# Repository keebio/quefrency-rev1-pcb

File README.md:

Quefrency Rev. 1 Keyboard PCB
=============================

Files are provided as-is, as I haven't fully had the chance to clean everything up. The working name of the Quefrency was Spectrogram, hence some of the files being marked with that name.

If anyone wants to clean things up, go ahead and submit a PR. Thanks!

License
-------
These files are released under the MIT License.

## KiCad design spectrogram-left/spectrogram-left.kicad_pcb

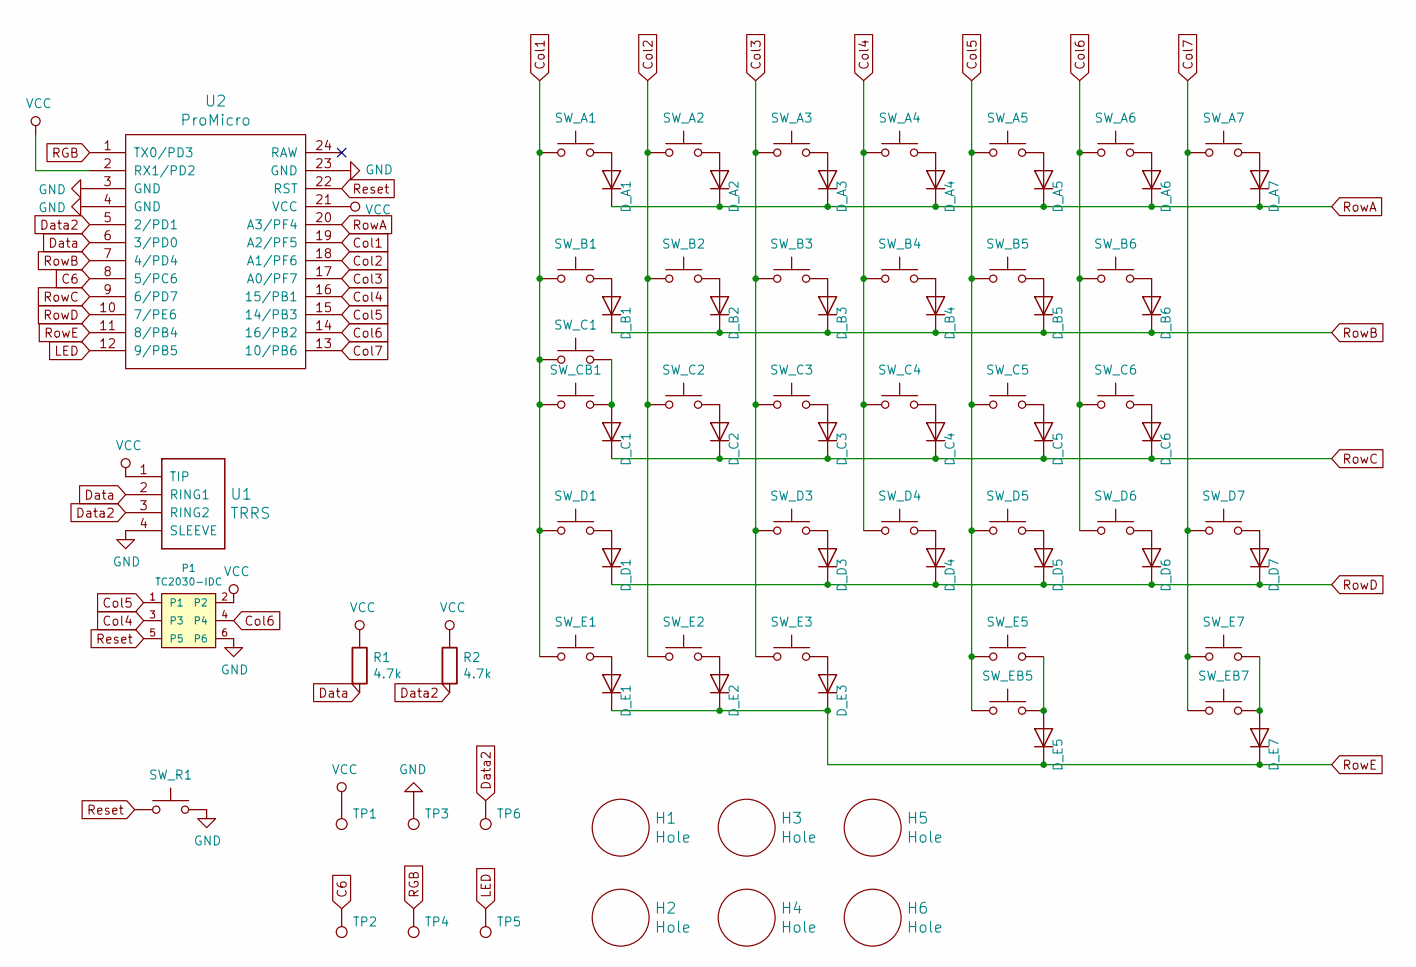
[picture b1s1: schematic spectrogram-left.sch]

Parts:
D_A1, D_A2, D_A3, D_A4, D_A5, D_A6, D_A7: D; Diode-Hybrid-Back
D_B1, D_B2, D_B3, D_B4, D_B5, D_B6: D; Diode-Hybrid-Back
D_C1, D_C2, D_C3, D_C4, D_C5, D_C6: D; Diode-Hybrid-Back
D_D1, D_D3, D_D4, D_D5, D_D6, D_D7: D; Diode-Hybrid-Back
D_E1, D_E2, D_E3, D_E5, D_E7: D; Diode-Hybrid-Back
H1, H2, H3, H4, H5, H6: Hole; MountingHole_3.2mm_M3_ISO14580_Pad
P1: TC2030-IDC; TC2030-NL_SMALL
R1, R2: 4.7k; Resistor-Hybrid-Back
SW_A1, SW_A2, SW_A3, SW_A4, SW_A5, SW_A6, SW_A7: SW_Push; MX-1U-NoLED
SW_B1: SW_Push; MX-1.5U-NoLED
SW_B2, SW_B3, SW_B4, SW_B5, SW_B6: SW_Push; MX-1U-NoLED
SW_C1: SW_Push; MX-1.75U-NoLED
SW_C2, SW_C3, SW_C4, SW_C5, SW_C6: SW_Push; MX-1U-NoLED
SW_CB1: SW_Push; MX-1.25U-NoLED
SW_D1: SW_Push; MX-2.25U-NoLED
SW_D3, SW_D4, SW_D5, SW_D6, SW_D7: SW_Push; MX-1U-NoLED
SW_E1, SW_E2, SW_E3, SW_E7: SW_Push; MX-1.25U-NoLED
SW_E5: SW_Push; MX-2.25U-ReversedStabilizers-NoLED
SW_EB5: SW_Push; MX-1.25U-NoLED
SW_EB7: SW_Push; MX-2.25U-ReversedStabilizers-NoLED
SW_R1: Reset; SW_Tactile_SPST_Angled_MJTP1117
TP1: VCC; SinglePad
TP2: C6; SinglePad
TP3: GND; SinglePad
TP4: RGB; SinglePad
TP5: LED; SinglePad
TP6: Extra Data; SinglePad
U1: TRRS; TRRS-PJ-320A
U2: ProMicro; ArduinoProMicro

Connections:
C6: TP2.1, U2.8 (5/PC6)
Col1: SW_A1.1, SW_B1.1, SW_C1.1, SW_CB1.2, SW_D1.1, SW_E1.1, U2.19 (A2/PF5)
Col2: SW_A2.1, SW_B2.1, SW_C2.1, SW_E2.1, U2.18 (A1/PF6)
Col3: SW_A3.1, SW_B3.1, SW_C3.1, SW_D3.1, SW_E3.1, U2.17 (A0/PF7)
Col4: P1.3, SW_A4.1, SW_B4.1, SW_C4.1, SW_D4.1, U2.16 (15/PB1)
Col5: P1.1, SW_A5.1, SW_B5.1, SW_C5.1, SW_D5.1, SW_E5.1, SW_EB5.1, U2.15 (14/PB3)
Col6: P1.4, SW_A6.1, SW_B6.1, SW_C6.1, SW_D6.1, U2.14 (16/PB2)
Col7: SW_A7.1, SW_D7.1, SW_E7.1, SW_EB7.1, U2.13 (10/PB6)
Data: R1.2, U1.2 (RING1), U2.6 (3/PD0)
Data2: R2.2, TP6.1, U1.3 (RING2), U2.5 (2/PD1)
GND: P1.6, SW_R1.2, TP3.1, U1.4 (SLEEVE), U2.3 (GND), U2.4 (GND), U2.23 (GND)
LED: TP5.1, U2.12 (9/PB5)
unnamed: D_A1.2 (A), SW_A1.2
unnamed: D_A2.2 (A), SW_A2.2
unnamed: D_A3.2 (A), SW_A3.2
unnamed: D_A4.2 (A), SW_A4.2
unnamed: D_A5.2 (A), SW_A5.2
unnamed: D_A6.2 (A), SW_A6.2
unnamed: D_A7.2 (A), SW_A7.2
unnamed: D_B1.2 (A), SW_B1.2
unnamed: D_B2.2 (A), SW_B2.2
unnamed: D_B3.2 (A), SW_B3.2
unnamed: D_B4.2 (A), SW_B4.2
unnamed: D_B5.2 (A), SW_B5.2
unnamed: D_B6.2 (A), SW_B6.2
unnamed: D_C1.2 (A), SW_C1.2, SW_CB1.1
unnamed: D_C2.2 (A), SW_C2.2
unnamed: D_C3.2 (A), SW_C3.2
unnamed: D_C4.2 (A), SW_C4.2
unnamed: D_C5.2 (A), SW_C5.2
unnamed: D_C6.2 (A), SW_C6.2
unnamed: D_D1.2 (A), SW_D1.2
unnamed: D_D3.2 (A), SW_D3.2
unnamed: D_D4.2 (A), SW_D4.2
unnamed: D_D5.2 (A), SW_D5.2
unnamed: D_D6.2 (A), SW_D6.2
unnamed: D_D7.2 (A), SW_D7.2
unnamed: D_E1.2 (A), SW_E1.2
unnamed: D_E2.2 (A), SW_E2.2
unnamed: D_E3.2 (A), SW_E3.2
unnamed: D_E5.2 (A), SW_E5.2, SW_EB5.2
unnamed: D_E7.2 (A), SW_E7.2, SW_EB7.2
RGB: TP4.1, U2.1 (TX0/PD3)
Reset: P1.5, SW_R1.1, U2.22 (RST)
RowA: D_A1.1 (K), D_A2.1 (K), D_A3.1 (K), D_A4.1 (K), D_A5.1 (K), D_A6.1 (K), D_A7.1 (K), U2.20 (A3/PF4)
RowB: D_B1.1 (K), D_B2.1 (K), D_B3.1 (K), D_B4.1 (K), D_B5.1 (K), D_B6.1 (K), U2.7 (4/PD4)
RowC: D_C1.1 (K), D_C2.1 (K), D_C3.1 (K), D_C4.1 (K), D_C5.1 (K), D_C6.1 (K), U2.9 (6/PD7)
RowD: D_D1.1 (K), D_D3.1 (K), D_D4.1 (K), D_D5.1 (K), D_D6.1 (K), D_D7.1 (K), U2.10 (7/PE6)
RowE: D_E1.1 (K), D_E2.1 (K), D_E3.1 (K), D_E5.1 (K), D_E7.1 (K), U2.11 (8/PB4)
VCC: P1.2, R1.1, R2.1, TP1.1, U1.1 (TIP), U2.2 (RX1/PD2), U2.21 (VCC)

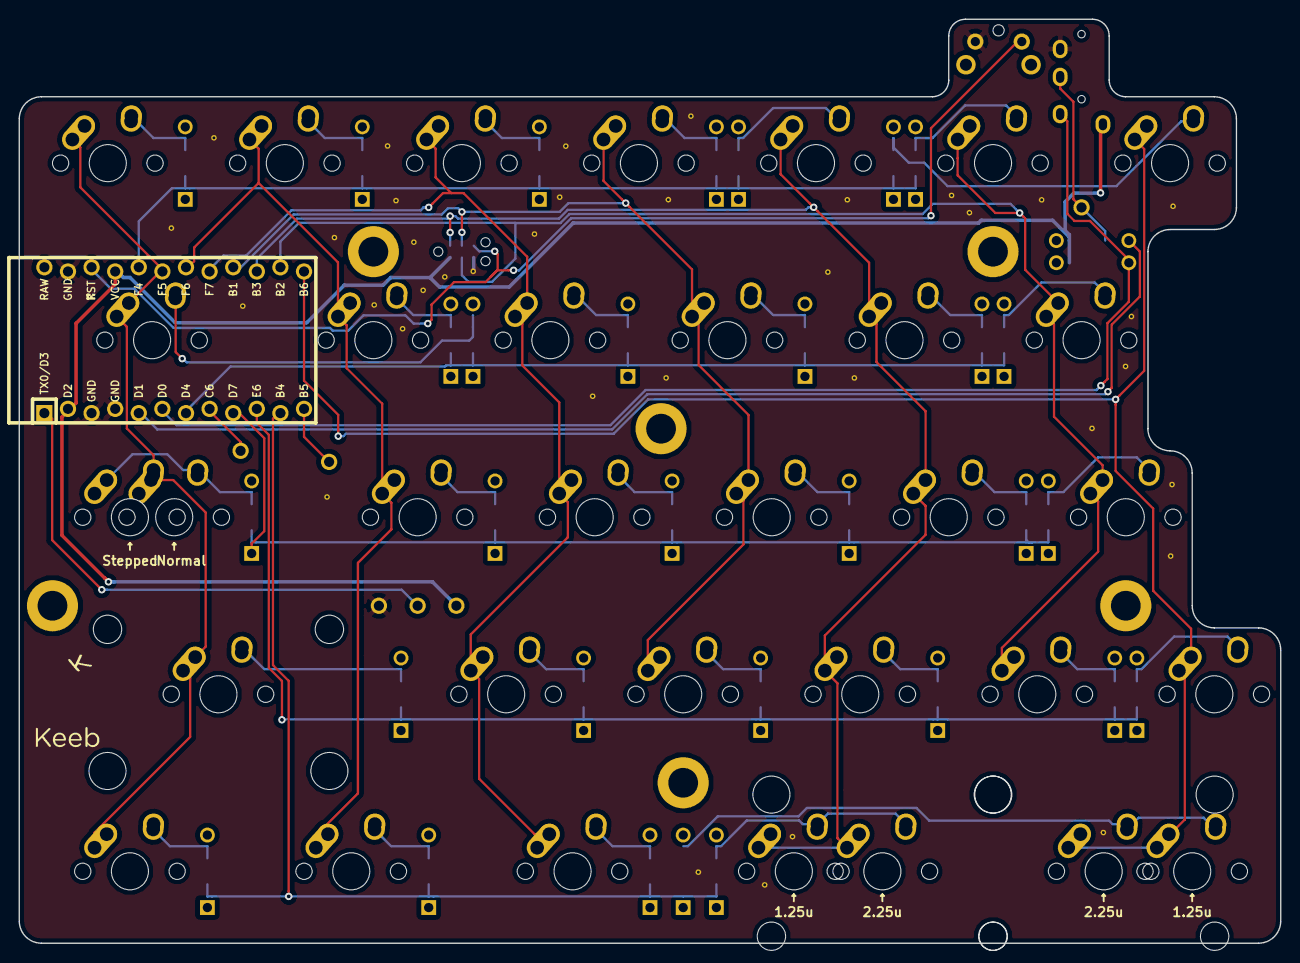
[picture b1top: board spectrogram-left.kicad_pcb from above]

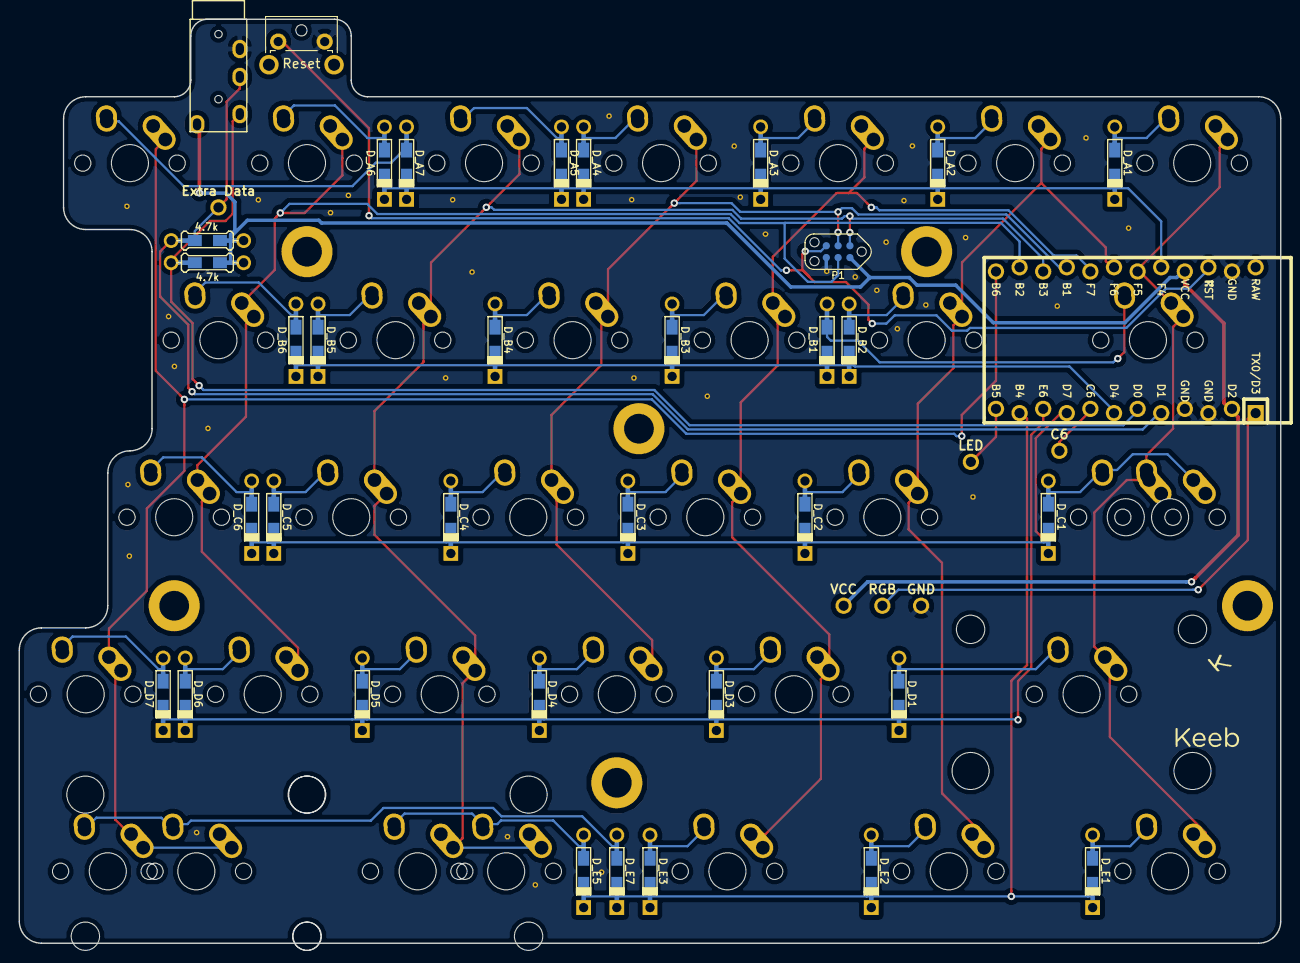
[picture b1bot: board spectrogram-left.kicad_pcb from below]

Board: 2 copper layers, 135.7 x 99.4 mm, 81 parts (9 on the bottom side), 50 nets.

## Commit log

2021-04-30 Initial commit of Quefrency files
